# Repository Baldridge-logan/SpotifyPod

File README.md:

# SpotifyPod
This is a code repository for the Spotify-Pod, a small PocketBeagle based music streaming device made for Rice University's ENGI 301 course.

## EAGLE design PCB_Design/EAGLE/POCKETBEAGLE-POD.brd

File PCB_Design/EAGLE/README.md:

This folder contains relevant EAGLE PCB design files. This custom PCB contains a PCM5102a DAC chip, TPS717 Linear Regulator, audio jack, USB-A connector, and connection pins for the TFT screen and Ipod Clickwheel.

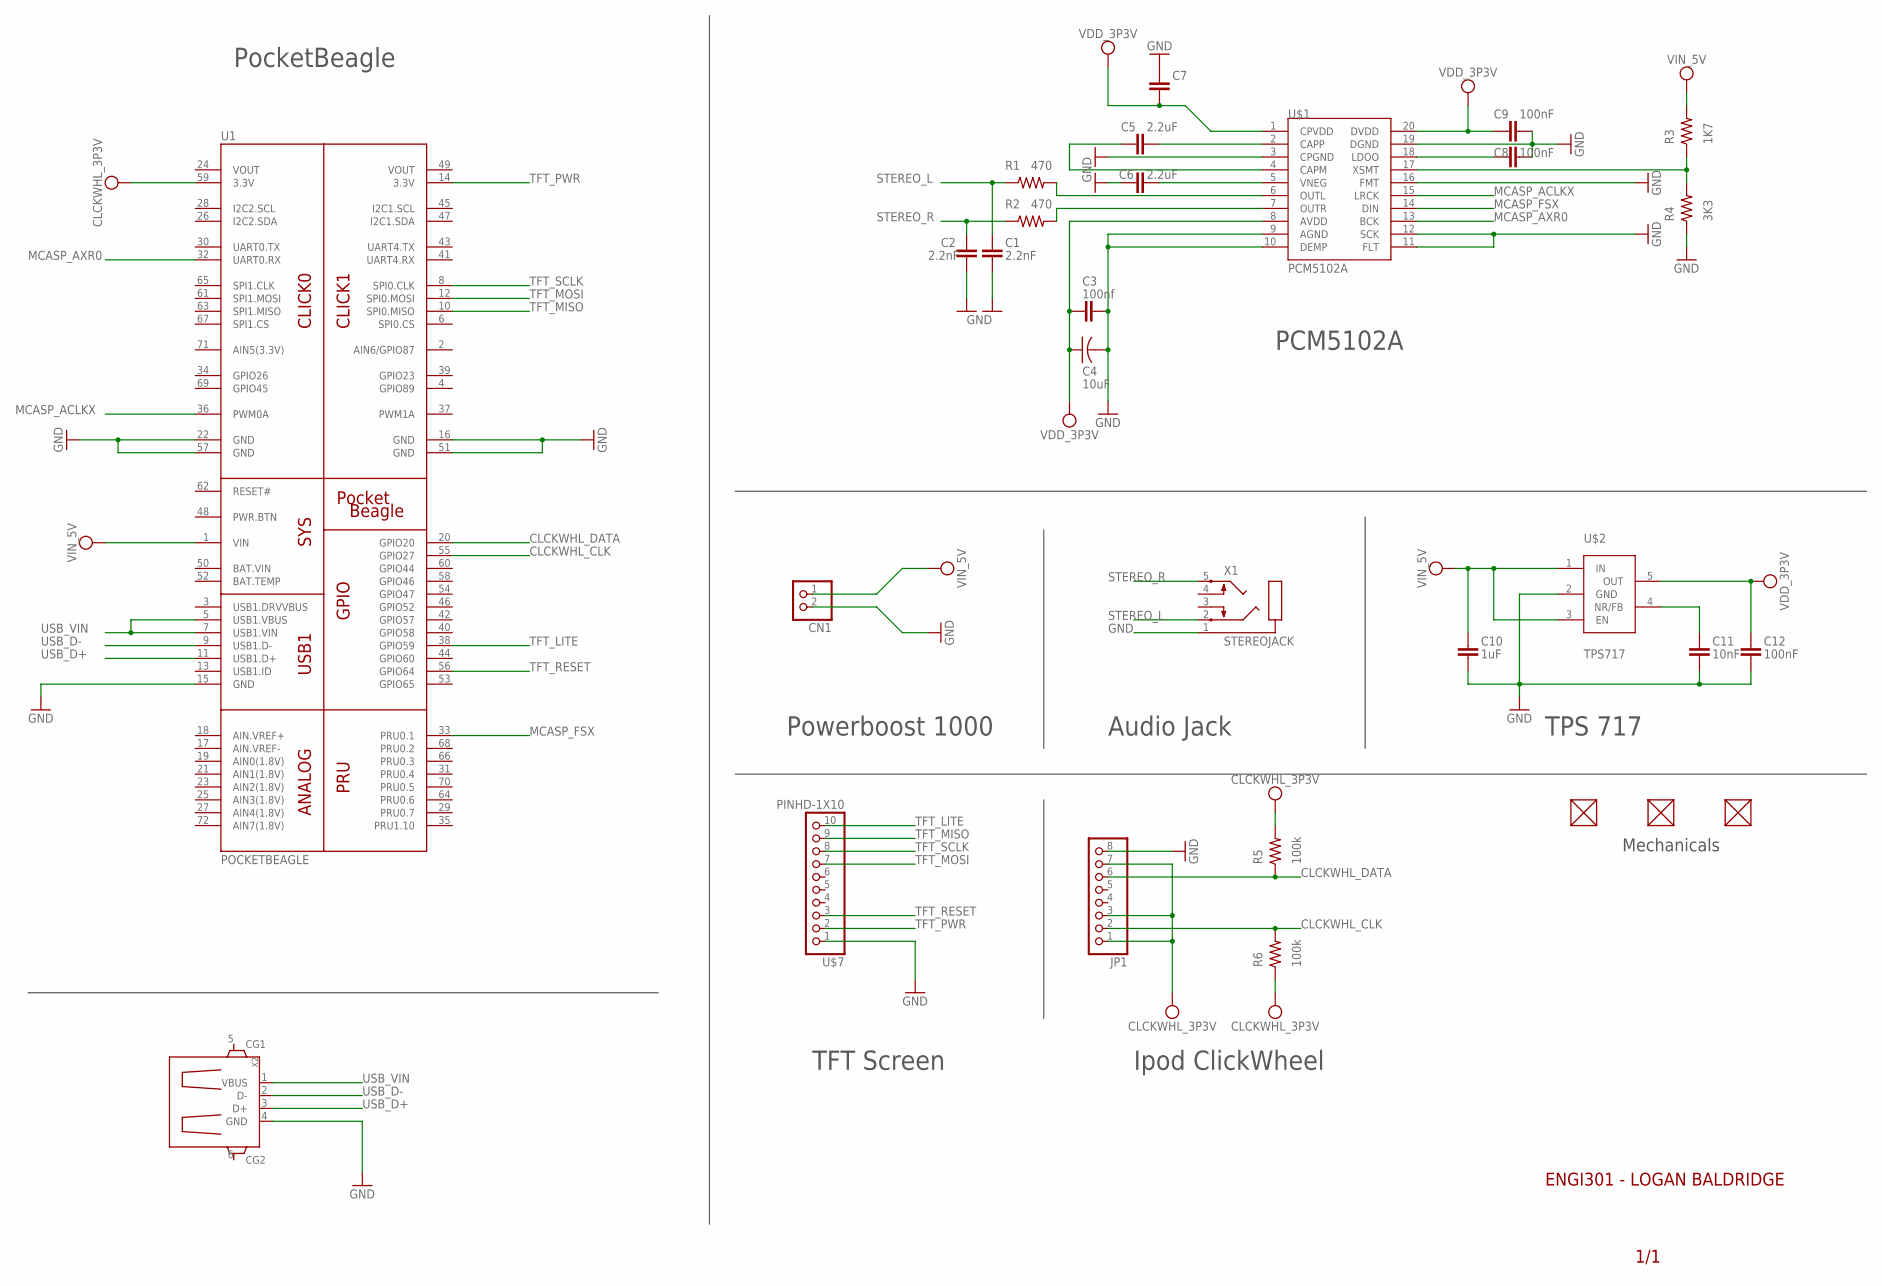
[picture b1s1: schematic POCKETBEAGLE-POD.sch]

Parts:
C1, C2: 2.2nF; C0402
C3: 100nf; C0402
C4: 10uF; C1005
C5, C6: 2.2uF; C0402
C7: C_C0402; C0402
C8, C9, C12: 100nF; C0402
C10: 1uF; C0402
C11: 10nF; C0402
CN1: 1; JST-PH-2-THM
FUD1, FUD2, FUD3: FIDUCIAL; FIDUCIAL_40MIL
JP1: PINHD-1X8BIG; 1X08-BIG
R1, R2: 470; R0402
R3: 1K7; R0402
R4: 3K3; R0402
R5, R6: 100k; R0402
U1: POCKETBEAGLE
U$1: PCM5102A
U$2: TPS717
U$7: PINHD-1X10; 1X10-BIG
X1: STEREOJACK; STX3100
X2: GHI2_USB_HOST_W/CHASSIS_GND; GHI2_USB_HOST_HORIZONTAL_W/CHASSIS_GND

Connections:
BAT.VIN: U1.50 (BAT.VIN)
CLCKWHL_3P3V: JP1.1, JP1.3, JP1.7, R5.2, R6.1, U1.59 (3.3V)
CLCKWHL_CLK: JP1.2, R6.2, U1.55 (GPIO27)
CLCKWHL_DATA: JP1.6, R5.1, U1.20 (GPIO20)
GND: C1.2, C2.1, C3.2, C4.2, C6.1, C7.1, C8.2, C9.2, C10.2, C11.2, C12.2, CN1.2 (1), JP1.8, R4.1, U1.15 (GND), U1.16 (GND), U1.22 (GND), U1.51 (GND), U1.57 (GND), U$1.3 (CPGND), U$1.9 (AGND), U$1.10 (DEMP), U$1.11 (FLT), U$1.12 (SCK), U$1.16 (FMT), U$1.19 (DGND), U$2.2 (GND), U$7.1, X1.1, X2.4 (GND)
MCASP_ACLKX: U1.36 (PWM0A), U$1.15 (LRCK)
MCASP_AXR0: U1.32 (UART0.RX), U$1.13 (BCK)
MCASP_FSX: U1.33 (PRU0.1), U$1.14 (DIN)
unnamed: R1.2, U$1.6 (OUTL)
unnamed: R2.2, U$1.7 (OUTR)
unnamed: C5.1, U$1.4 (CAPM)
unnamed: C5.2, U$1.2 (CAPP)
unnamed: C6.2, U$1.5 (VNEG)
unnamed: R3.1, R4.2, U$1.17 (XSMT)
unnamed: C7.2, U$1.1 (CPVDD)
unnamed: C11.1, U$2.4 (NR/FB)
unnamed: C8.1, U$1.18 (LDOO)
STEREO_L: C1.1, R1.1, X1.2
STEREO_R: C2.2, R2.1, X1.5
TFT_LITE: U1.38 (GPIO59), U$7.10
TFT_MISO: U1.10 (SPI0.MISO), U$7.9
TFT_MOSI: U1.12 (SPI0.MOSI), U$7.7
TFT_PWR: U1.14 (3.3V), U$7.2
TFT_RESET: U1.56 (GPIO64), U$7.3
TFT_SCLK: U1.8 (SPI0.CLK), U$7.8
USB_D+: U1.11 (USB1.D+), X2.3 (D+)
USB_D-: U1.9 (USB1.D-), X2.2 (D-)
USB_VIN: U1.5 (USB1.VBUS), U1.7 (USB1.VIN), X2.1 (VBUS)
VDD_3P3V: C3.1, C4.1, C9.1, C12.1, U$1.8 (AVDD), U$1.20 (DVDD), U$2.5 (OUT)
VIN_5V: C10.1, CN1.1 (2), R3.2, U$2.1 (IN), U$2.3 (EN)
VOUT: U1.24 (VOUT), U1.49 (VOUT)

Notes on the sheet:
ENGI301 - LOGAN BALDRIDGE
1/1
PocketBeagle
TFT Screen
Ipod ClickWheel
Powerboost 1000
Audio Jack
PCM5102A
TPS 717
Mechanicals

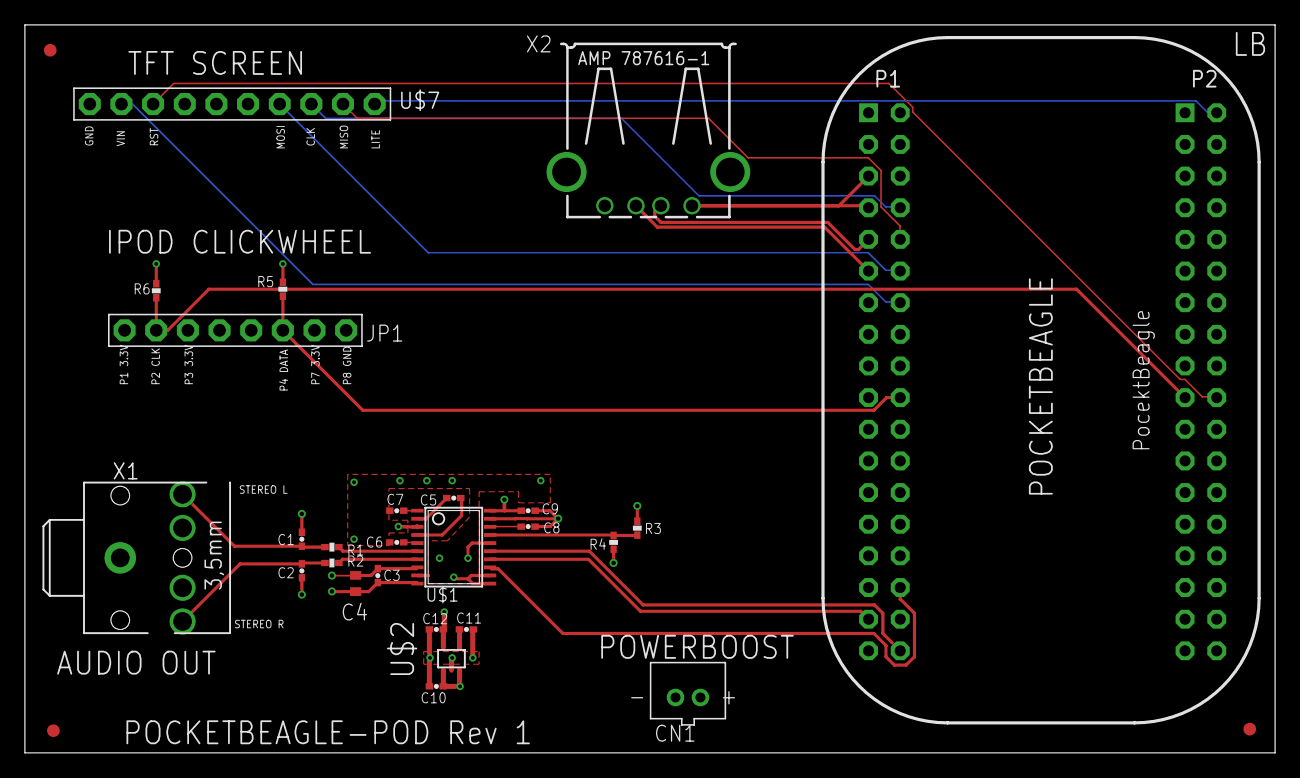
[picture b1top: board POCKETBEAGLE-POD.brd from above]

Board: 4 copper layers, 100.3 x 58.4 mm, 29 parts (0 on the bottom side), 30 nets.

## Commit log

2018-11-13 Add files via upload
    Initial Commit
2018-11-15 License Update
2018-11-15 Rename PB-PimorroniPHAT_v05.dts to PB-PimoroniPHAT_v05.dts
2018-12-12 Documentation Fixes
2018-12-12 Intial Commit
2018-12-12 More documentation fixes
